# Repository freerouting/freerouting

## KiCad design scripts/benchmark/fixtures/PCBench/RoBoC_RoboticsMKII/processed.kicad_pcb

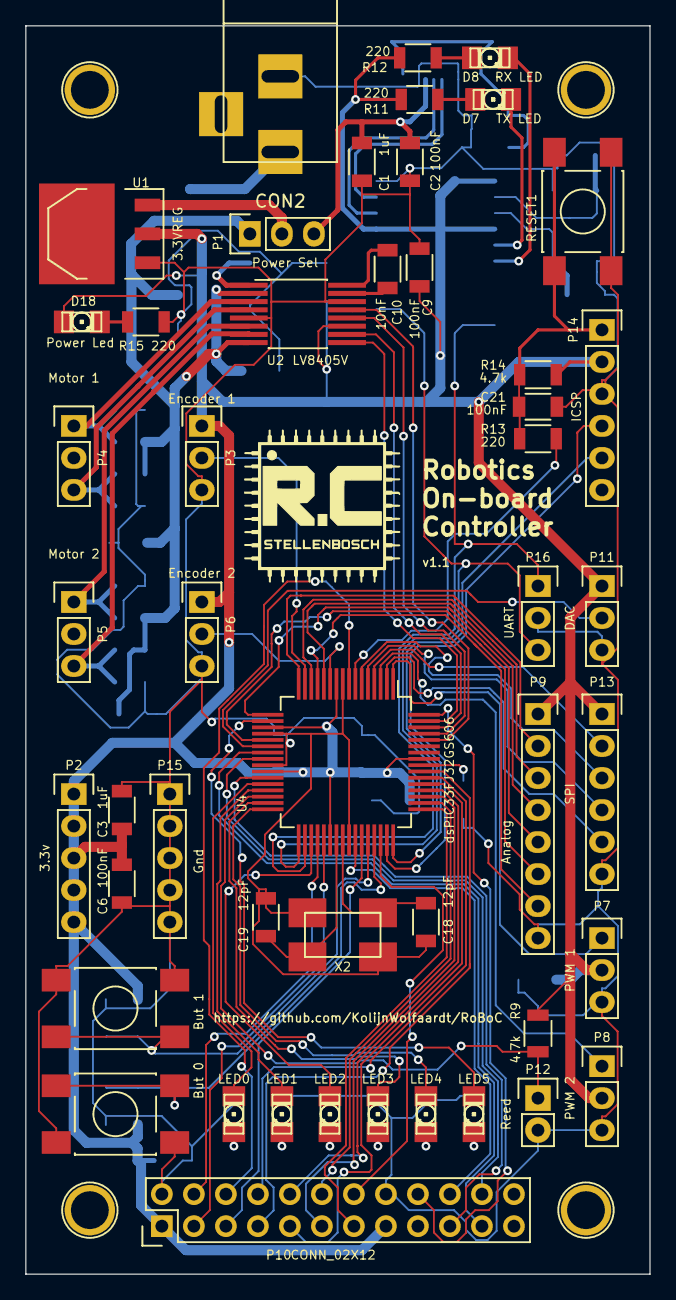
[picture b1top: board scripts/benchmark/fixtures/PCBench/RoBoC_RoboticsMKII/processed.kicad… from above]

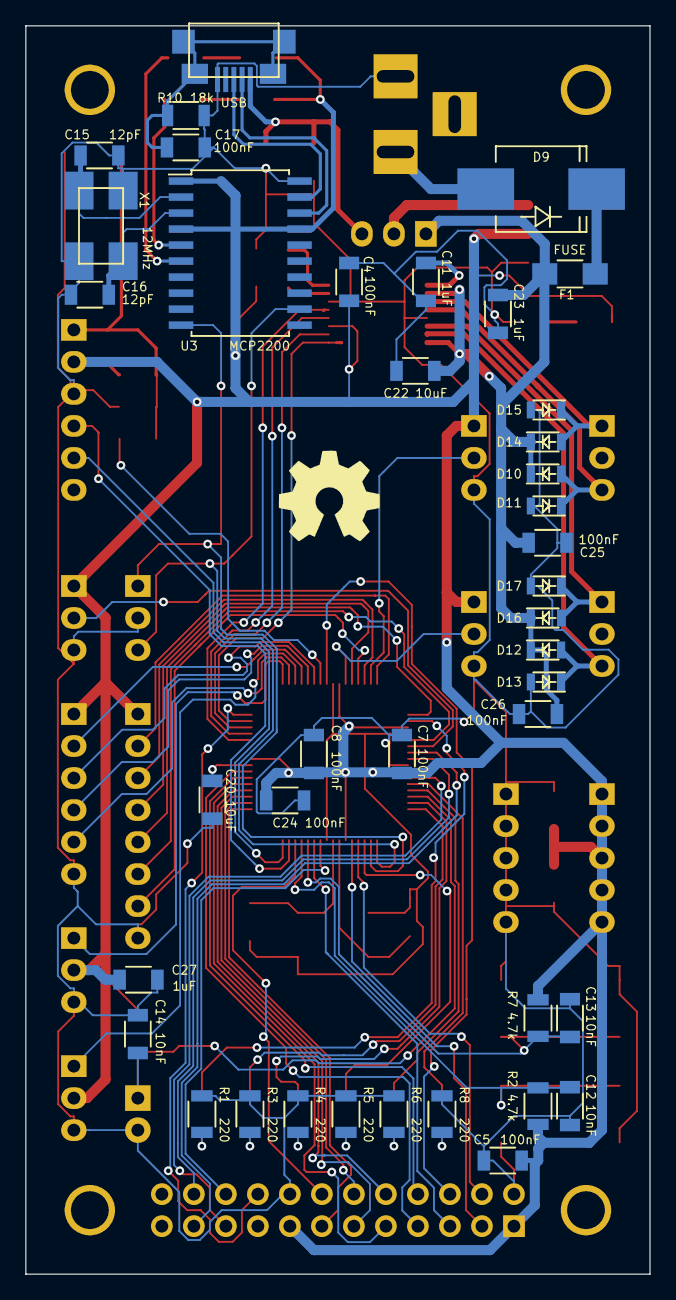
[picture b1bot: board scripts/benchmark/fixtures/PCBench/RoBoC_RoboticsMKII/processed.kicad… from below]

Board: 2 copper layers, 49.5 x 99.1 mm, 92 parts (40 on the bottom side), 84 nets.

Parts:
C1, C3, C4, C23, C27: 1uF; C_1206
C2, C5, C6, C7, C8, C9, C11, C17, C21, C24, C25, C26: 100nF; C_1206
C10, C12, C13, C14: 10nF; C_1206
C15, C16, C18, C19: 12pF; C_1206
C20, C22: 10uF; C_1206
CON1: USB; USB_Micro
CON2: BARREL_JACK
D1: LED5; LED-1206
D2: LED4; LED-1206
D3: LED3; LED-1206
D4: LED2; LED-1206
D5: LED1; LED-1206
D6: LED0; LED-1206
D7: TX LED; LED-1206
D8: RX LED; LED-1206
D9: D; Diode-SMC_Handsoldering
D10, D11, D12, D13, D14, D15, D16, D17: D; SOD-323
D18: Power Led; LED-1206
F1: FUSE; R_1206_HandSoldering
P1: Power Sel; Pin_Header_Straight_1x03
P2: 3.3v; Pin_Header_Straight_1x05
P3: Encoder 1; Pin_Header_Straight_1x03
P4: Motor 1; Pin_Header_Straight_1x03
P5: Motor 2; Pin_Header_Straight_1x03
P6: Encoder 2; Pin_Header_Straight_1x03
P7: PWM 1; Pin_Header_Straight_1x03
P8: PWM 2; Pin_Header_Straight_1x03
P9: Analog; Pin_Header_Straight_1x08
P10: CONN_02X12; Pin_Header_Straight_2x12
P11: DAC; Pin_Header_Straight_1x03
P12: Reed; Pin_Header_Straight_1x02
P13: SPI; Pin_Header_Straight_1x06
P14: ICSP; Pin_Header_Straight_1x06
P15: Gnd; Pin_Header_Straight_1x05
P16: UART; Pin_Header_Straight_1x03
P96, P97, P98, P99: CONN_01X01; MountingHole3mm
R1, R3, R4, R5, R6, R8, R11, R12, R13, R15: 220; R_1206
R2, R7, R9, R14: 4.7k; R_1206
R10: 18k; R_1206
RESET1: DPST; SW_SPST_bigpads
SW0: But 0; SW_SPST_bigpads
SW1: But 1; SW_SPST_bigpads
U1: 3.3VREG; SOT-223
U2: LV8405V; SSOP-16_4.4x5.2mm_Pitch0.65mm_Handsoldering
U3: MCP2200; SOIC-20_7.5x12.8mm_Pitch1.27mm
U4: dsPIC33FJ32GS606; TQFP-64_10x10mm_Pitch0.5mm_handsoldering
X1: 12MHz; Crystal 6x 3.5 x 1.1mm
X2: 10MHz; Crystal 6x 3.5 x 1.1mm

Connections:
/gpio/AN0: P9.2, U4.16
/gpio/AN1: P9.3, U4.14
/gpio/AN2: P9.4, U4.12
/gpio/AN3: P9.5, U4.17
/gpio/AN4: P9.6, U4.21
/gpio/AN5: P9.7, U4.13
/gpio/BUT_0: C12.2, R2.2, SW0.1, U4.45
/gpio/BUT_1: C13.2, R7.2, SW1.1, U4.44
/gpio/DACOUT: P11.2, U4.22
/gpio/DATA_0: P10.14, U4.46
/gpio/DATA_1: P10.13, U4.49
/gpio/DATA_2: P10.12, U4.50
/gpio/DATA_3: P10.11, U4.51
/gpio/DATA_4: P10.10, U4.52
/gpio/DATA_5: P10.9, U4.53
/gpio/DATA_6: P10.8, U4.54
/gpio/DATA_7: P10.7, U4.55
/gpio/Href: P10.6, U4.8
/gpio/LED0: D6.1, U4.28
/gpio/LED1: D5.1, U4.29
/gpio/LED2: D4.1, U4.35
/gpio/LED3: D3.1, U4.31
/gpio/LED4: D2.1, U4.32
/gpio/LED5: D1.1, U4.18
/gpio/RCK: P10.18, U4.64
/gpio/Reed: C14.2, P12.1, R9.2, U4.30
/gpio/SIO_C: P10.3, U4.37
/gpio/SIO_D: P10.4, U4.36
/gpio/SPI_CLK: P13.2, U4.4
/gpio/SPI_MISO: P13.4, U4.5
/gpio/SPI_MOSI: P13.3, U4.6
/gpio/SPI_SS: P13.5, U4.2
/gpio/vSync: P10.5, U4.43
/gpio/~OE: P10.20, U4.42
/gpio/~RRST: P10.22, U4.24
/gpio/~WR: P10.19, U4.27
/gpio/~WRST: P10.21, U4.23
/mcu/MCLR: R13.2, U4.7
/mcu/MCLR_in: C21.1, P14.1, R13.1, R14.1, RESET1.1
/mcu/MOT1_D1: U2.13, U4.60
/mcu/MOT1_D2: U2.12, U4.61
/mcu/MOT1_ENC: P3.2, U4.15
/mcu/MOT2_D1: U2.10, U4.62
/mcu/MOT2_D2: U2.9, U4.63
/mcu/MOT2_ENC: P6.2, U4.11
/mcu/OSC1: C18.2, U4.40, X2.1
/mcu/OSC2: C19.2, U4.39, X2.2
/mcu/PGC: P14.5, U4.48
/mcu/PGD: P14.4, U4.47
/mcu/Vcap: C20.2, U4.56
/motors/C1H: C10.1, U2.16
/motors/C1L: C10.2, U2.15
/motors/MOT1_1: D14.1, D15.2, P4.1, U2.3
/motors/MOT1_2: D10.1, D11.2, P4.3, U2.4
/motors/MOT2_1: D16.1, D17.2, P5.1, U2.6
/motors/MOT2_2: D12.1, D13.2, P5.3, U2.7
/motors/PWM1: P7.1, U4.1
/motors/PWM2: P8.1, U4.3
/motors/VG: C11.1, U2.1
/motors/V_Bat: C22.1, C23.1, C25.1, C26.1, D10.2, D12.2, D14.2, D16.2, F1.2, P1.1, U2.2, U2.8
/power/V_USB: C1.1, C2.1, CON1.1, P1.3
/usb/MCU_RX: P16.1, U3.10, U4.34
/usb/MCU_TX: P16.3, U3.12, U4.33
/usb/RX_LED: D8.2, U3.6
/usb/TX_LED: D7.2, U3.5
/usb/USB_D+: CON1.3, U3.19
/usb/USB_D-: CON1.2, U3.18
/usb/USB_OSC1: C15.1, U3.2, X1.1
/usb/USB_OSC2: C16.1, U3.3, X1.2
GND: C1.2, C2.2, C3.2, C4.2, C5.2, C6.2, C7.2, C8.2, C9.2, C11.2, C12.1, C13.1, C14.1, C15.2, C16.2, C17.2, C18.1, C19.1, C20.1, C21.2, C22.2, C23.2, C24.2, C25.2, C26.2, C27.2, CON1.5, CON2.2, D11.1, D13.1, D15.1, D17.1, P3.3, P6.3, P7.3, P8.3, P9.8, P10.2, P10.16, P11.3, P12.2, P13.6, P14.3, P15.1, P15.2, P15.3, P15.4, P15.5, P16.2, R1.2, R3.2, R4.2, R5.2, R6.2, R8.2, R10.2, R15.2, RESET1.2, SW0.2, SW1.2, U1.1, U2.5, U2.14, U3.20, U4.9, U4.20, U4.25, U4.41, X1.3, X2.3
unnamed: C17.1, CON1.6, CON1.7, CON1.8, CON1.9, R10.1
unnamed: CON2.1, D9.1
unnamed: D1.2, R1.1
unnamed: D2.2, R3.1
unnamed: D3.2, R4.1
unnamed: D4.2, R5.1
unnamed: D5.2, R6.1
unnamed: D6.2, R8.1
unnamed: D7.1, R11.2
unnamed: D8.1, R12.2
unnamed: D9.2, F1.1
unnamed: D18.2, R15.1
unnamed: P1.2, U1.3
V3.3: C3.1, C4.1, C5.1, C6.1, C7.1, C8.1, C9.1, C24.1, C27.1, D18.1, P2.1, P2.2, P2.3, P2.4, P2.5, P3.1, P6.1, P7.2, P8.2, P9.1, P10.1, P10.15, P11.1, P13.1, P14.2, R2.1, R7.1, R9.1, R11.1, R12.1, R14.2, U1.2, U2.11, U3.1, U3.4, U3.17, U4.10, U4.19, U4.26, U4.38, U4.57

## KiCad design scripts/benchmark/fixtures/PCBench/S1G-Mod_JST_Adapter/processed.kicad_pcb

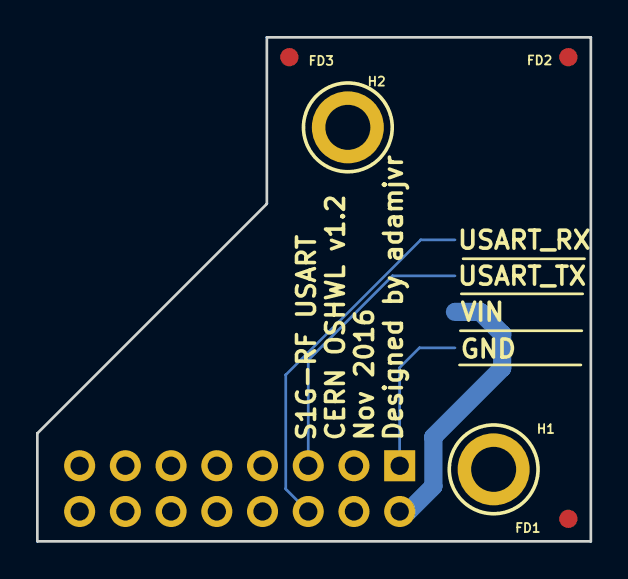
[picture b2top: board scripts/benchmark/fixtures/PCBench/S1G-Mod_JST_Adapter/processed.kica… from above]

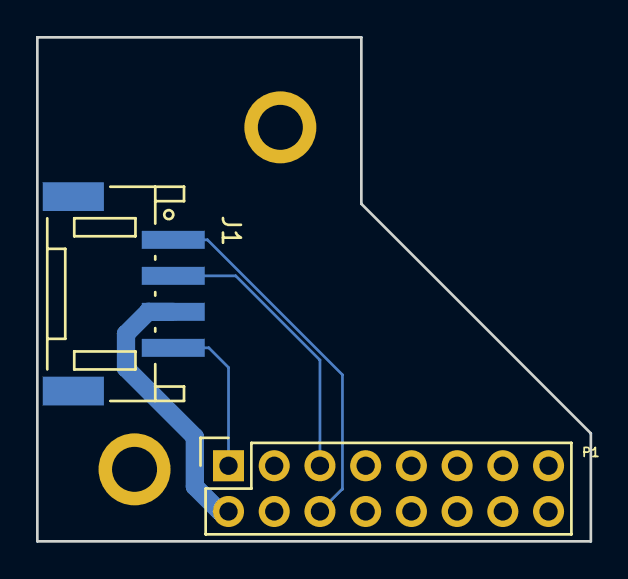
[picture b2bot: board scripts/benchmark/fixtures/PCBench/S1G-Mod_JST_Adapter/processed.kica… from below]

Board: 2 copper layers, 30.8 x 28.0 mm, 7 parts (2 on the bottom side), 4 nets.

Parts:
FD1, FD2, FD3: FIDUCIAL
H1, H2: M2.5_Hole; M2.5_HOLE
J1: S4B-PH-SM4-TB(LF)(SN)
P1: CONN_02X08; Socket_Strip_Straight_2x08

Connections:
/USART1_RX: J1.1, P1.6
/USART1_TX: J1.2, P1.5
/VIN: J1.3, P1.2
GND: J1.4, P1.1

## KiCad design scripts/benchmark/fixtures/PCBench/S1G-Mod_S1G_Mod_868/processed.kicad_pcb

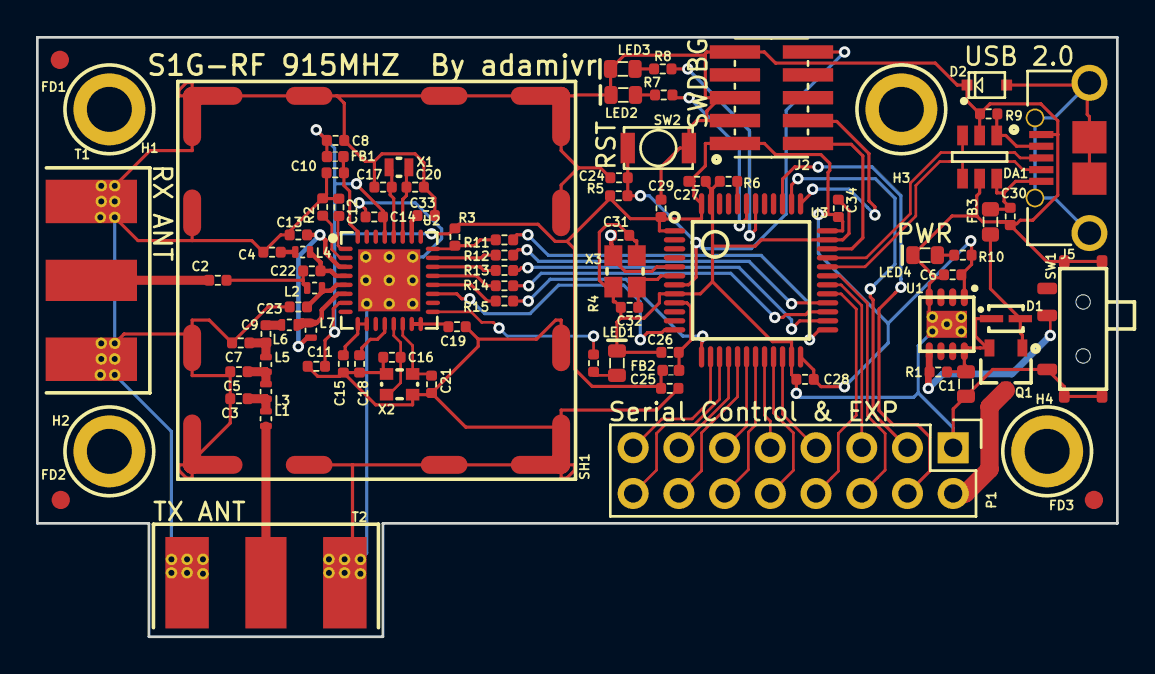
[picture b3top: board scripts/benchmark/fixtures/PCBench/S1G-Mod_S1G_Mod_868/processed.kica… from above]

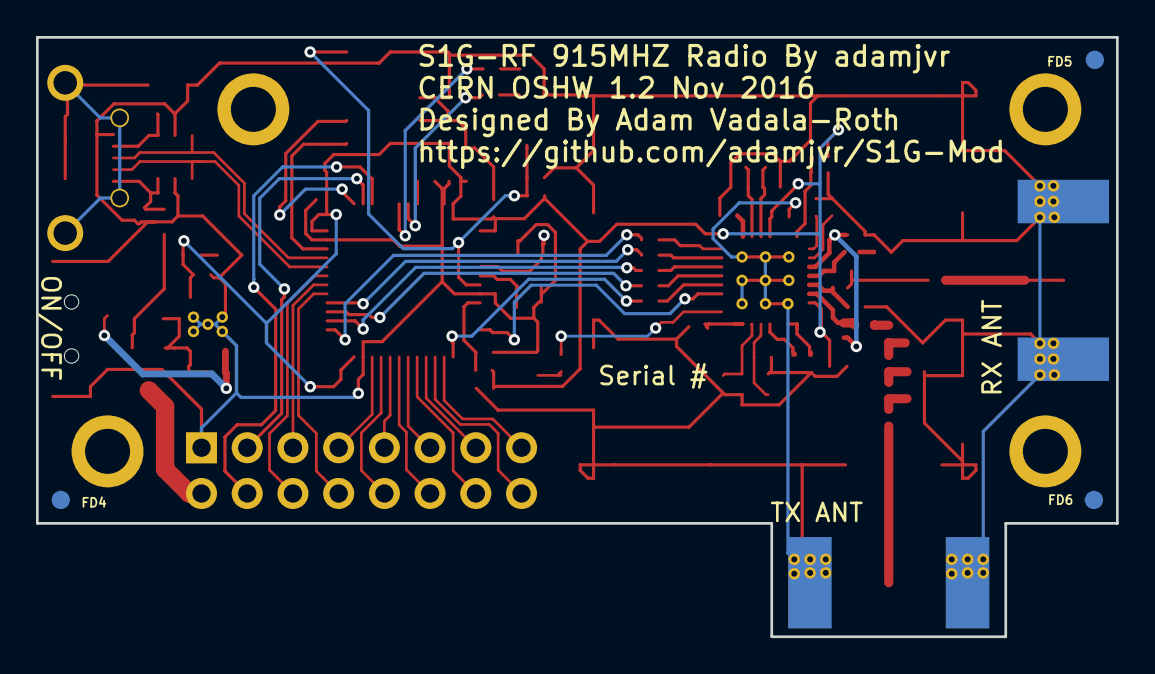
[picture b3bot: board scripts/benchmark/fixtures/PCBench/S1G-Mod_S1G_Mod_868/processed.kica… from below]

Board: 4 copper layers, 60.0 x 33.3 mm, 91 parts (3 on the bottom side), 73 nets.

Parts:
C1: CL10A106KQ8NNNC; C0603
C2: CBR04C560F1GAC; C0402
C3, C5: GJM1555C1H2R2WB01D; C0402
C4: GRM1555C1H101GA01D; C0402
C6, C8, C10, C11, C14, C24, C25, C26, C27, C28, C29, C30, C34: CL05B104JP5NNNC; C0402
C7: GJM1555C1H1R0BB01D; C0402
C9: CBR04C470F3GAC; C0402
C12, C13, C15, C19, C33: CL10B224JO8NNNC; C0402
C16, C21, C31, C32: GRM0225C1E8R0WA03L; C0402
C17, C20: CL05C090CB5NNNC; C0402
C18: GRM155R71H152KA01D; C0402
C22: GRM1555C2A2R7CA01D; C0402
C23: GRM1555C1E1R2BA01D; C0402
D1: BAT20JFILM
D2: RSB39VTE-17
DA1: ESDA6V1BC6
FB1, FB2: BLM15HG601SN1D
FB3: MI0603K300R-10
FD1, FD2, FD3, FD4, FD5, FD6: FIDUCIAL
H1, H2, H3, H4: M2.5_Hole; M2.5_HOLE
J2: 20021121-00010C4LF
J5: 0475890001-MicroUSBPort; 0475890001
L1, L2, L5: 0402CS-12NXJL; L0402
L3: 0402CS-24NXJL; L0402
L4: 0402CS-6N2XJL; L0402
L6: 0402CS-1N8XJL; L0402
L7: 0402CS-47NXJL; L0402
LED1, LED2: LTST-C193TBKT-5A; LED0603
LED3: LTST-C191KGKT; LED0603
LED4: LTST-C193KRKT-5A; LED0603
P1: 61301621121
Q1: DMG2307L-7
R1, R3, R6: RC1005F103CS; R0402
R2: ERA-2AEB363X; R0402
R4, R5, R7, R8, R10: RC1005F102CS; R0402
R9: RC1005J473CS; R0402
R11, R12, R13, R14, R15: TNPW0402100RBEED; R0402
SH1: 36103205
SW1: CUS-12TB
SW2: B3U-1000P
T1, T2: 732511150; 0732511150
U1: AP7361-33FGE-7
U2: ADF7023BCPZ
U3: STM32L052C8T6
X1: ABS05-32.768KHZ-9-T
X2: ABM11-140-26.000MHZ-T3
X3: ABM10-166-12.000MHZ-T3

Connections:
+3V3: C6.1, C8.2, C11.1, C14.2, C25.1, C27.1, C28.1, C29.1, C34.1, FB1.1, FB2.1, J2.1, R3.1, R5.1, R10.2, U1.1, U2.7, U2.29, U3.1, U3.24, U3.36, U3.48
/GPIO2: U2.19, U3.12
/MCU - STM32L052K8T6/GPIO_PA8: P1.8, U3.29
/MCU - STM32L052K8T6/GPIO_PA15: P1.3, U3.38
/MCU - STM32L052K8T6/GPIO_PB0: P1.11, U3.18
/MCU - STM32L052K8T6/GPIO_PB1: P1.12, U3.19
/MCU - STM32L052K8T6/GPIO_PB2: P1.9, U3.20
/MCU - STM32L052K8T6/GPIO_PB3: P1.4, U3.39
/MCU - STM32L052K8T6/GPIO_PB10: P1.10, U3.21
/MCU - STM32L052K8T6/GPIO_PB11: P1.7, U3.22
/MCU - STM32L052K8T6/MCU_IRQ: R15.2, U3.13
/MCU - STM32L052K8T6/NRST: C24.1, J2.10, R5.2, SW2.2, U3.7
/MCU - STM32L052K8T6/SPI2_MISO: P1.13, U3.16
/MCU - STM32L052K8T6/SPI2_MOSI: P1.14, U3.17
/MCU - STM32L052K8T6/SPI2_NSS: P1.15, U3.14
/MCU - STM32L052K8T6/SPI2_SCLK: P1.16, U3.15
/MCU - STM32L052K8T6/SPI_CS: R11.2, U3.25
/MCU - STM32L052K8T6/SPI_MISO: R14.2, U3.27
/MCU - STM32L052K8T6/SPI_MOSI: R12.2, U3.28
/MCU - STM32L052K8T6/SPI_SCLK: R13.2, U3.26
/MCU - STM32L052K8T6/SWCLK: J2.4, U3.37
/MCU - STM32L052K8T6/SWDIO: J2.2, U3.34
/MCU - STM32L052K8T6/USART1_RX: P1.6, U3.31
/MCU - STM32L052K8T6/USART1_TX: P1.5, U3.30
/MCU - STM32L052K8T6/USB_DM: DA1.4, J5.2, U3.32
/MCU - STM32L052K8T6/USB_DP: DA1.3, J5.3, U3.33
/MCU_IRQ: R15.1, U2.20
/ON_OFF: R1.1, SW1.2, U1.5
/PSU_IN: P1.2, Q1.3
/SPI_CS: R3.2, R11.1, U2.24
/SPI_MISO: R14.1, U2.21
/SPI_MOSI: R12.1, U2.23
/SPI_SCLK: R13.1, U2.22
/VBUS: D1.1, FB3.1, Q1.1
/VIN: C1.1, D1.2, Q1.2, R1.2, U1.8
/VREF: C10.2, FB1.2, U2.32
GND: C1.2, C3.2, C4.1, C5.2, C6.2, C7.2, C8.1, C10.1, C11.2, C12.1, C13.1, C14.1, C15.2, C16.2, C17.1, C18.2, C19.2, C20.2, C21.2, C23.1, C24.2, C25.2, C26.2, C27.2, C28.2, C29.2, C30.1, C31.2, C32.2, C33.2, C34.2, D2.2, DA1.2, DA1.5, J2.3, J2.5, J2.9, J5.5, LED1.2, LED2.2, LED3.2, LED4.2, P1.1, R2.1, R6.1, R9.2, SH1.1, SW1.1, SW1.4, SW2.1, T1.2, T2.2, U1.4, U1.9, U2.33, U3.8, U3.23, U3.35, U3.47, X2.2, X2.4, X3.2, X3.4
unnamed: C2.1, T1.1
unnamed: C2.2, C22.1, L2.1
unnamed: C3.1, L1.2, L3.1
unnamed: C4.2, L4.1
unnamed: C5.1, L3.2, L5.1
unnamed: C7.1, C9.1, L5.2
unnamed: C9.2, L6.1
unnamed: C12.2, U2.1
unnamed: C13.2, L7.1, U2.3
unnamed: C15.1, U2.9, U2.10
unnamed: C16.1, U2.13, X2.1
unnamed: C17.2, U2.28, X1.1
unnamed: C18.1, U2.12
unnamed: C19.1, U2.15, U2.16
unnamed: C20.1, U2.27, X1.2
unnamed: C21.1, U2.14, X2.3
unnamed: C22.2, L4.2, U2.4
unnamed: C23.2, L2.2, U2.5
unnamed: C26.1, FB2.2, U3.9
unnamed: C30.2, DA1.6, FB3.2, J5.1
unnamed: C31.1, U3.5, X3.1
unnamed: C32.1, U3.6, X3.3
unnamed: C33.1, U2.26
unnamed: D2.1, J5.6, J5.7, J5.8, J5.9, J5.10, J5.11
unnamed: DA1.1, J5.4, R9.1
unnamed: L1.1, T2.1
unnamed: L6.2, L7.2, U2.6
unnamed: LED1.1, R4.2
unnamed: LED2.1, R7.1
unnamed: LED3.1, R8.1
unnamed: LED4.1, R10.1
unnamed: R2.2, U2.2
unnamed: R4.1, U2.17
unnamed: R6.2, U3.44
unnamed: R7.2, U3.43
unnamed: R8.2, U3.42
